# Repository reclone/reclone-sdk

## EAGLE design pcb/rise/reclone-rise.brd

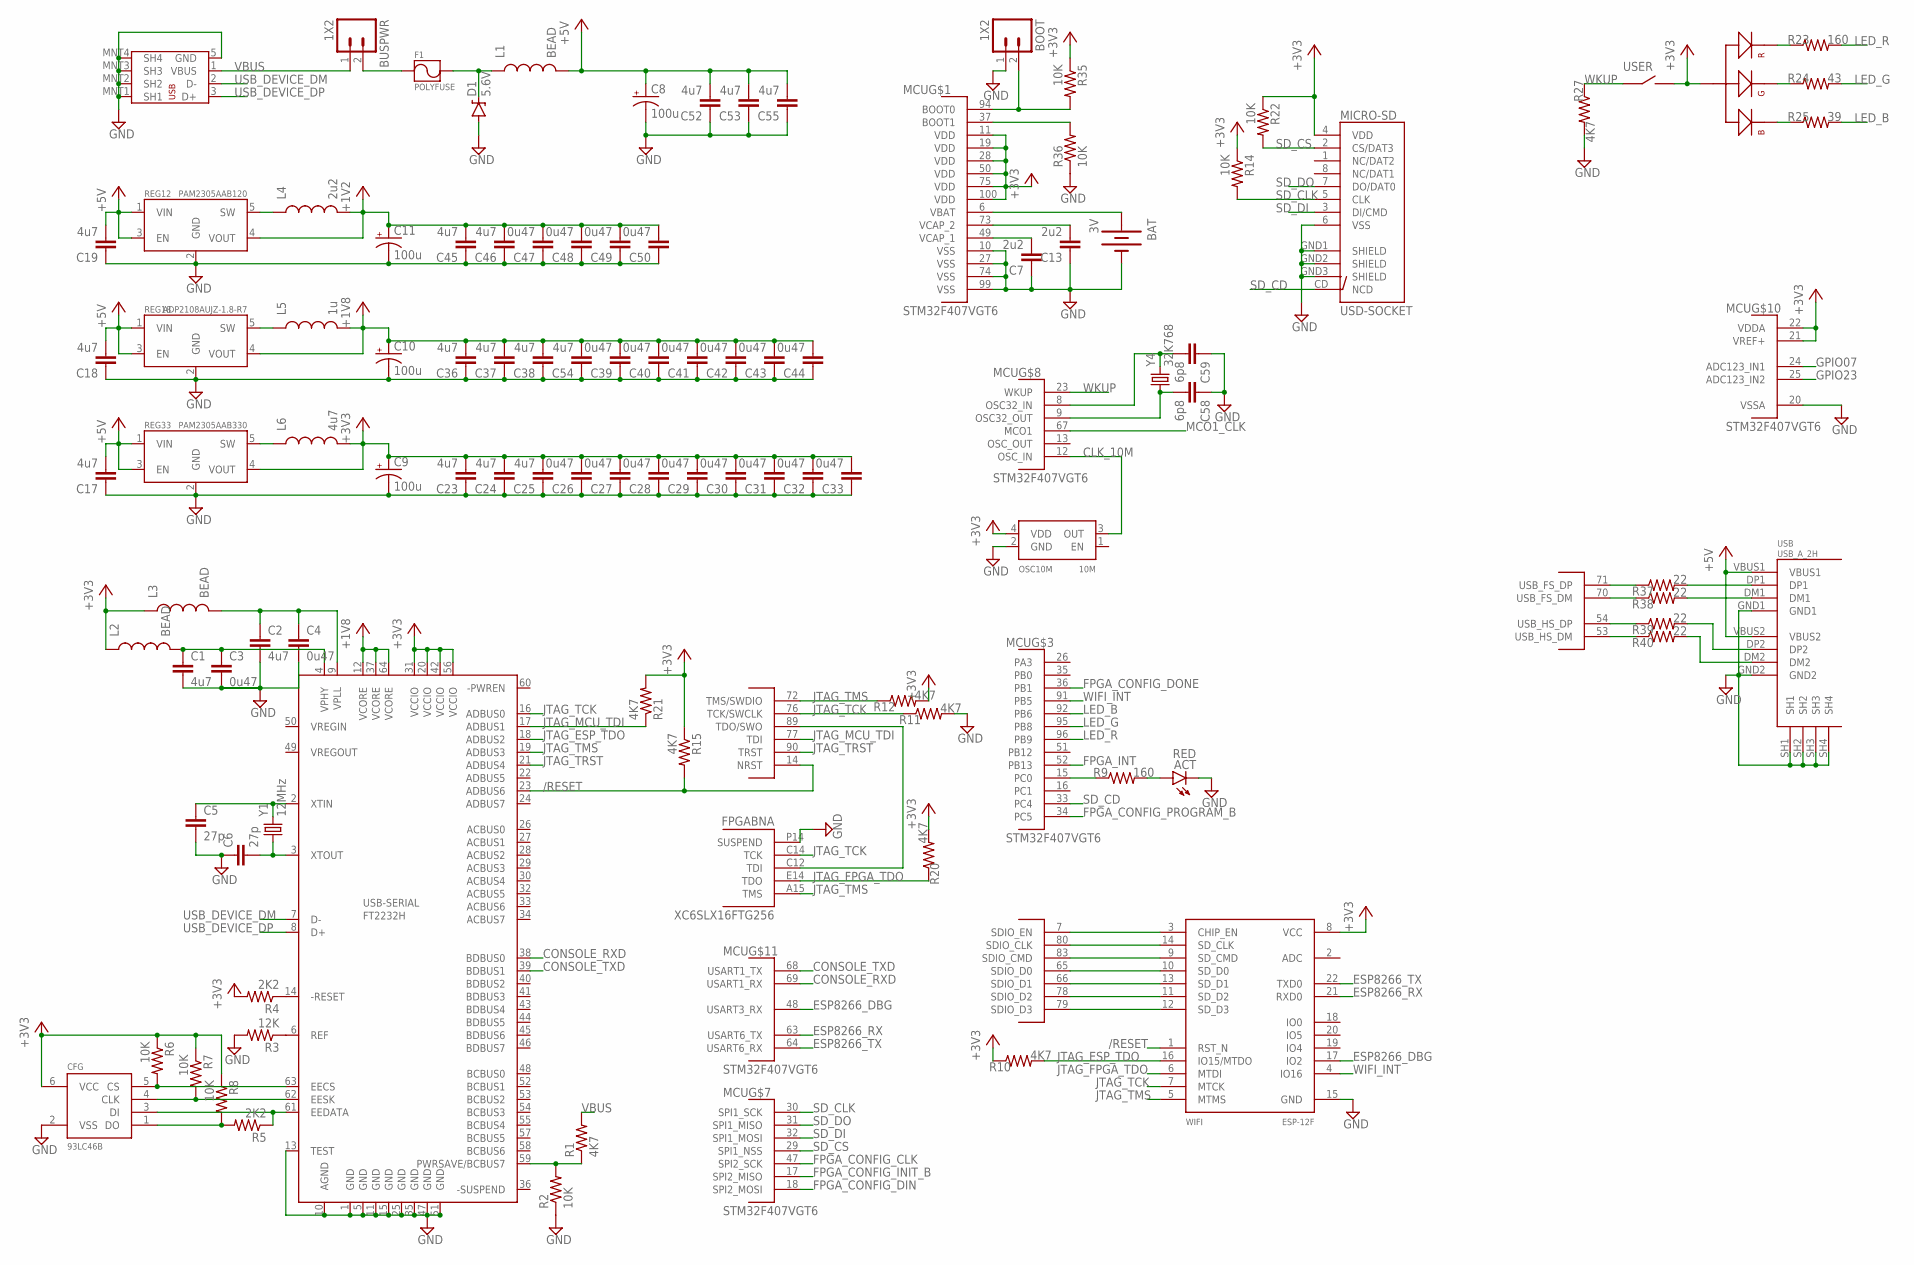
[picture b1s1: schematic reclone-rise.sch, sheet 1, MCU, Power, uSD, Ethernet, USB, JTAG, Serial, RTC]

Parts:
ACT: RED; LED-0603
BAT: 3V; BATTCON_12MM; DIGIKEY# BK-885-ND
BOOT: 1X2; 1X02; DIGIKEY# 952-1770-ND
BUSPWR: 1X2; 1X02; DIGIKEY# 952-1770-ND
C1, C2, C17, C18, C19, C23, C24, C25, C36, C37, C38, C45, C46, C52, C53, C54, C55: 4u7; 0603-CAP
C3, C4, C26, C27, C28, C29, C30, C31, C32, C33, C39, C40, C41, C42, C43, C44, C47, C48, C49, C50: 0u47; 0603-CAP
C5, C6: 27p; 0603-CAP
C7, C13: 2u2; 0603-CAP
C8, C9, C10, C11: 100u; EIA3216
C58, C59: 6p8; 0603-CAP
CFG: 93LC46B; SOT-23-6; DIGIKEY# 93LC46BT-I/OTCT-ND
D1: 5.6V; SOD-323
DEBUG: USB-MICRO-B-SMD; DIGIKEY# 609-4618-1-ND
F1: POLYFUSE; 1206L; DIGIKEY# MF-NSMF150-2CT-ND
FPGA: XC6SLX16FTG256; FT256; DIGIKEY# 122-1672-ND
L1, L2, L3: BEAD; 0603
L4: 2u2; 0603
L5: 1u; 0603
L6: 4u7; 0603
MCU: STM32F407VGT6; LQFP-100
MICRO-SD: USD-SOCKET; MICRO-SD-SOCKET-PP; DIGIKEY# 101-00660-68-6-1-ND
OSC10M: 10M; OSC-5X3.2; DIGIKEY# 631-1436-1-ND
R1, R10, R11, R12, R15, R20, R21, R27: 4K7; 0603-RES
R2, R6, R7, R8, R14, R22, R35, R36: 10K; 0603-RES
R3: 12K; 0603-RES
R4, R5: 2K2; 0603-RES
R9, R23: 160; 0603-RES
R24: 43; 0603-RES
R25: 39; 0603-RES
R37, R38, R39, R40: 22; 0603-RES
REG12: PAM2305AAB120; SOT-23-5; DIGIKEY# PAM2305AAB120DICT-ND
REG18: ADP2108AUJZ-1.8-R7; SOT-23-5; DIGIKEY# ADP2108AUJZ-1.8-R7CT-ND
REG33: PAM2305AAB330; SOT-23-5; DIGIKEY# PAM2305AAB330DICT-ND
RGB: OVSRRGBCC3; RGB_LED_1204_RTANG; DIGIKEY# 365-1410-1-ND
USB: USB_A_2H; USB-A-2H
USB-SERIAL: FT2232H; TQFP64-12X12; DIGIKEY# 768-1024-1-ND
USER: TL1105SF250Q; PB_TACT_RTANG; DIGIKEY# EG1840-ND
WIFI: ESP-12F
Y1: 12MHz; CRYSTAL-SMD-5X3
Y4: 32K768; CRYSTAL-32KHZ-SMD_EPSON_MC146

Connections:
+1V2: C11.A (+), C45.2, C46.2, C47.2, C48.2, C49.2, C50.2, L4.2, REG12.4 (VOUT); also elsewhere on the board
+1V8: C10.A (+), C36.2, C37.2, C38.2, C39.2, C40.2, C41.2, C42.2, C43.2, C44.2, C54.2, L5.2, REG18.4 (VOUT), USB-SERIAL.12 (VCORE), USB-SERIAL.37 (VCORE), USB-SERIAL.64 (VCORE); also elsewhere on the board
+3V3: C9.A (+), C23.2, C24.2, C25.2, C26.2, C27.2, C28.2, C29.2, C30.2, C31.2, C32.2, C33.2, CFG.6 (VCC), L2.1, L3.1, L6.2, MCU.11 (VDD), MCU.19 (VDD), MCU.21 (VREF+), MCU.22 (VDDA), MCU.28 (VDD), MCU.50 (VDD), MCU.75 (VDD), MCU.100 (VDD), MICRO-SD.4 (VDD), OSC10M.4 (VDD), R4.2, R6.1, R7.1, R8.1, R10.1, R12.2, R14.1, R15.1, R20.2, R21.2, R22.1, R35.1, REG33.4 (VOUT), RGB.4 (ANODE), USB-SERIAL.20 (VCCIO), USB-SERIAL.31 (VCCIO), USB-SERIAL.42 (VCCIO), USB-SERIAL.56 (VCCIO), USER.SW_B (B), WIFI.8 (VCC); also elsewhere on the board
+5V: C8.A (+), C17.2, C18.2, C19.2, C52.2, C53.2, C55.2, L1.2, REG12.1 (VIN), REG12.3 (EN), REG18.1 (VIN), REG18.3 (EN), REG33.1 (VIN), REG33.3 (EN), USB.VBUS1, USB.VBUS2; also elsewhere on the board
/RESET: MCU.14 (NRST), R15.2, USB-SERIAL.23 (ADBUS6), WIFI.1 (RST_N)
BOOT0: BOOT.2, MCU.94 (BOOT0), R35.2
BOOT1: MCU.37 (BOOT1), R36.2
CLK_10M: MCU.12 (OSC_IN), OSC10M.3 (OUT); also elsewhere on the board
CONSOLE_RXD: MCU.69 (USART1_RX), USB-SERIAL.38 (BDBUS0)
CONSOLE_TXD: MCU.68 (USART1_TX), USB-SERIAL.39 (BDBUS1)
ESP8266_DBG: MCU.48 (USART3_RX), WIFI.17 (IO2)
ESP8266_RX: MCU.63 (USART6_TX), WIFI.21 (RXD0)
ESP8266_TX: MCU.64 (USART6_RX), WIFI.22 (TXD0)
ESP_CH_EN: MCU.7 (SDIO_EN), WIFI.3 (CHIP_EN)
FPGA_CONFIG_CLK: MCU.47 (SPI2_SCK); also elsewhere on the board
FPGA_CONFIG_DIN: MCU.18 (SPI2_MOSI); also elsewhere on the board
FPGA_CONFIG_DONE: MCU.36 (PB1); also elsewhere on the board
FPGA_CONFIG_INIT_B: MCU.17 (SPI2_MISO); also elsewhere on the board
FPGA_CONFIG_PROGRAM_B: MCU.34 (PC5); also elsewhere on the board
FPGA_INT: MCU.52 (PB13); also elsewhere on the board
GND: ACT.C, BAT.GND (-), BOOT.1, C1.2, C2.2, C3.2, C4.2, C5.2, C6.1, C7.1, C8.C (-), C9.C (-), C10.C (-), C11.C (-), C13.1, C17.1, C18.1, C19.1, C23.1, C24.1, C25.1, C26.1, C27.1, C28.1, C29.1, C30.1, C31.1, C32.1, C33.1, C36.1, C37.1, C38.1, C39.1, C40.1, C41.1, C42.1, C43.1, C44.1, C45.1, C46.1, C47.1, C48.1, C49.1, C50.1, C52.1, C53.1, C54.1, C55.1, C58.1, C59.1, CFG.2 (VSS), D1.A, DEBUG.5 (GND), DEBUG.MNT1 (SH1), DEBUG.MNT2 (SH2), DEBUG.MNT3 (SH3), DEBUG.MNT4 (SH4), FPGA.P14 (SUSPEND), MCU.10 (VSS), MCU.20 (VSSA), MCU.27 (VSS), MCU.74 (VSS), MCU.99 (VSS), MICRO-SD.6 (VSS), MICRO-SD.GND1 (SHIELD), MICRO-SD.GND2 (SHIELD), MICRO-SD.GND3 (SHIELD), OSC10M.2 (GND), R2.1, R3.2, R11.2, R27.2, R36.1, REG12.2 (GND), REG18.2 (GND), REG33.2 (GND), USB.GND1, USB.GND2, USB.SH1, USB.SH2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; also elsewhere on the board
GPIO07: MCU.24 (ADC123_IN1); also elsewhere on the board
GPIO23: MCU.25 (ADC123_IN2); also elsewhere on the board
JTAG_ESP_TDO: R10.2, USB-SERIAL.18 (ADBUS2), WIFI.16 (IO15/MTDO)
JTAG_FPGA_TDO: FPGA.E14 (TDO), R20.1, WIFI.6 (MTDI)
JTAG_MCU_TDI: MCU.77 (TDI), R21.1, USB-SERIAL.17 (ADBUS1)
JTAG_MCU_TDO: FPGA.C12 (TDI), MCU.89 (TDO/SWO)
JTAG_TCK: FPGA.C14 (TCK), MCU.76 (TCK/SWCLK), R11.1, USB-SERIAL.16 (ADBUS0), WIFI.7 (MTCK)
JTAG_TMS: FPGA.A15 (TMS), MCU.72 (TMS/SWDIO), R12.1, USB-SERIAL.19 (ADBUS3), WIFI.5 (MTMS)
JTAG_TRST: MCU.90 (TRST), USB-SERIAL.21 (ADBUS4)
LED_ACT: MCU.15 (PC0), R9.1
LED_B: MCU.92 (PB6), R25.2
LED_G: MCU.95 (PB8), R24.2
LED_R: MCU.96 (PB9), R23.2
MCO1_CLK: MCU.67 (MCO1); also elsewhere on the board
unnamed: MCU.71 (USB_FS_DP), R37.1
unnamed: MCU.70 (USB_FS_DM), R38.1
unnamed: MCU.54 (USB_HS_DP), R39.1
unnamed: MCU.53 (USB_HS_DM), R40.1
unnamed: R40.2, USB.DM2
unnamed: R39.2, USB.DP2
unnamed: R1.1, R2.2, USB-SERIAL.59 (PWRSAVE/BCBUS7)
unnamed: R3.1, USB-SERIAL.6 (REF)
unnamed: R4.1, USB-SERIAL.14 (-RESET)
unnamed: CFG.1 (DO), R5.2, R8.2
unnamed: CFG.3 (DI), R5.1, USB-SERIAL.61 (EEDATA)
unnamed: CFG.4 (CLK), R7.2, USB-SERIAL.62 (EESK)
unnamed: CFG.5 (CS), R6.2, USB-SERIAL.63 (EECS)
unnamed: C2.1, C4.1, L3.2, USB-SERIAL.9 (VPLL)
unnamed: C1.1, C3.1, L2.2, USB-SERIAL.4 (VPHY)
unnamed: C6.2, USB-SERIAL.3 (XTOUT), Y1.1
unnamed: C5.1, USB-SERIAL.2 (XTIN), Y1.3 (2)
unnamed: R23.1, RGB.1 (R)
unnamed: R24.1, RGB.2 (G)
unnamed: R25.1, RGB.3 (B)
unnamed: C58.2, MCU.9 (OSC32_OUT), Y4.P$2 (1)
unnamed: C59.2, MCU.8 (OSC32_IN), Y4.P$1 (2)
unnamed: R37.2, USB.DP1
unnamed: BUSPWR.2, F1.1
unnamed: ACT.A, R9.2
unnamed: R38.2, USB.DM1
unnamed: D1.C, F1.2, L1.1
unnamed: L4.1, REG12.5 (SW)
unnamed: L5.1, REG18.5 (SW)
unnamed: L6.1, REG33.5 (SW)
SDIO_CLK: MCU.80 (SDIO_CLK), WIFI.14 (SD_CLK)
SDIO_CMD: MCU.83 (SDIO_CMD), WIFI.9 (SD_CMD)
SDIO_D0: MCU.65 (SDIO_D0), WIFI.10 (SD_D0)
SDIO_D1: MCU.66 (SDIO_D1), WIFI.13 (SD_D1)
SDIO_D2: MCU.78 (SDIO_D2), WIFI.11 (SD_D2)
SDIO_D3: MCU.79 (SDIO_D3), WIFI.12 (SD_D3)
SD_CD: MCU.33 (PC4), MICRO-SD.CD (NCD)
SD_CLK: MCU.30 (SPI1_SCK), MICRO-SD.5 (CLK), R14.2
SD_CS: MCU.29 (SPI1_NSS), MICRO-SD.2 (CS/DAT3), R22.2
SD_DI: MCU.32 (SPI1_MOSI), MICRO-SD.3 (DI/CMD)
SD_DO: MCU.31 (SPI1_MISO), MICRO-SD.7 (DO/DAT0)
USB_DEVICE_DM: DEBUG.2 (D-), USB-SERIAL.7 (D-)
USB_DEVICE_DP: DEBUG.3 (D+), USB-SERIAL.8 (D+)
VBAT: BAT.PWR@1 (+), MCU.6 (VBAT)
VBUS: BUSPWR.1, DEBUG.1 (VBUS), R1.2
VCAP_1: C7.2, MCU.49 (VCAP_1)
VCAP_2: C13.2, MCU.73 (VCAP_2)
WIFI_INT: MCU.91 (PB5), WIFI.4 (IO16)
WKUP: MCU.23 (WKUP), R27.1, USER.SW_A (A)

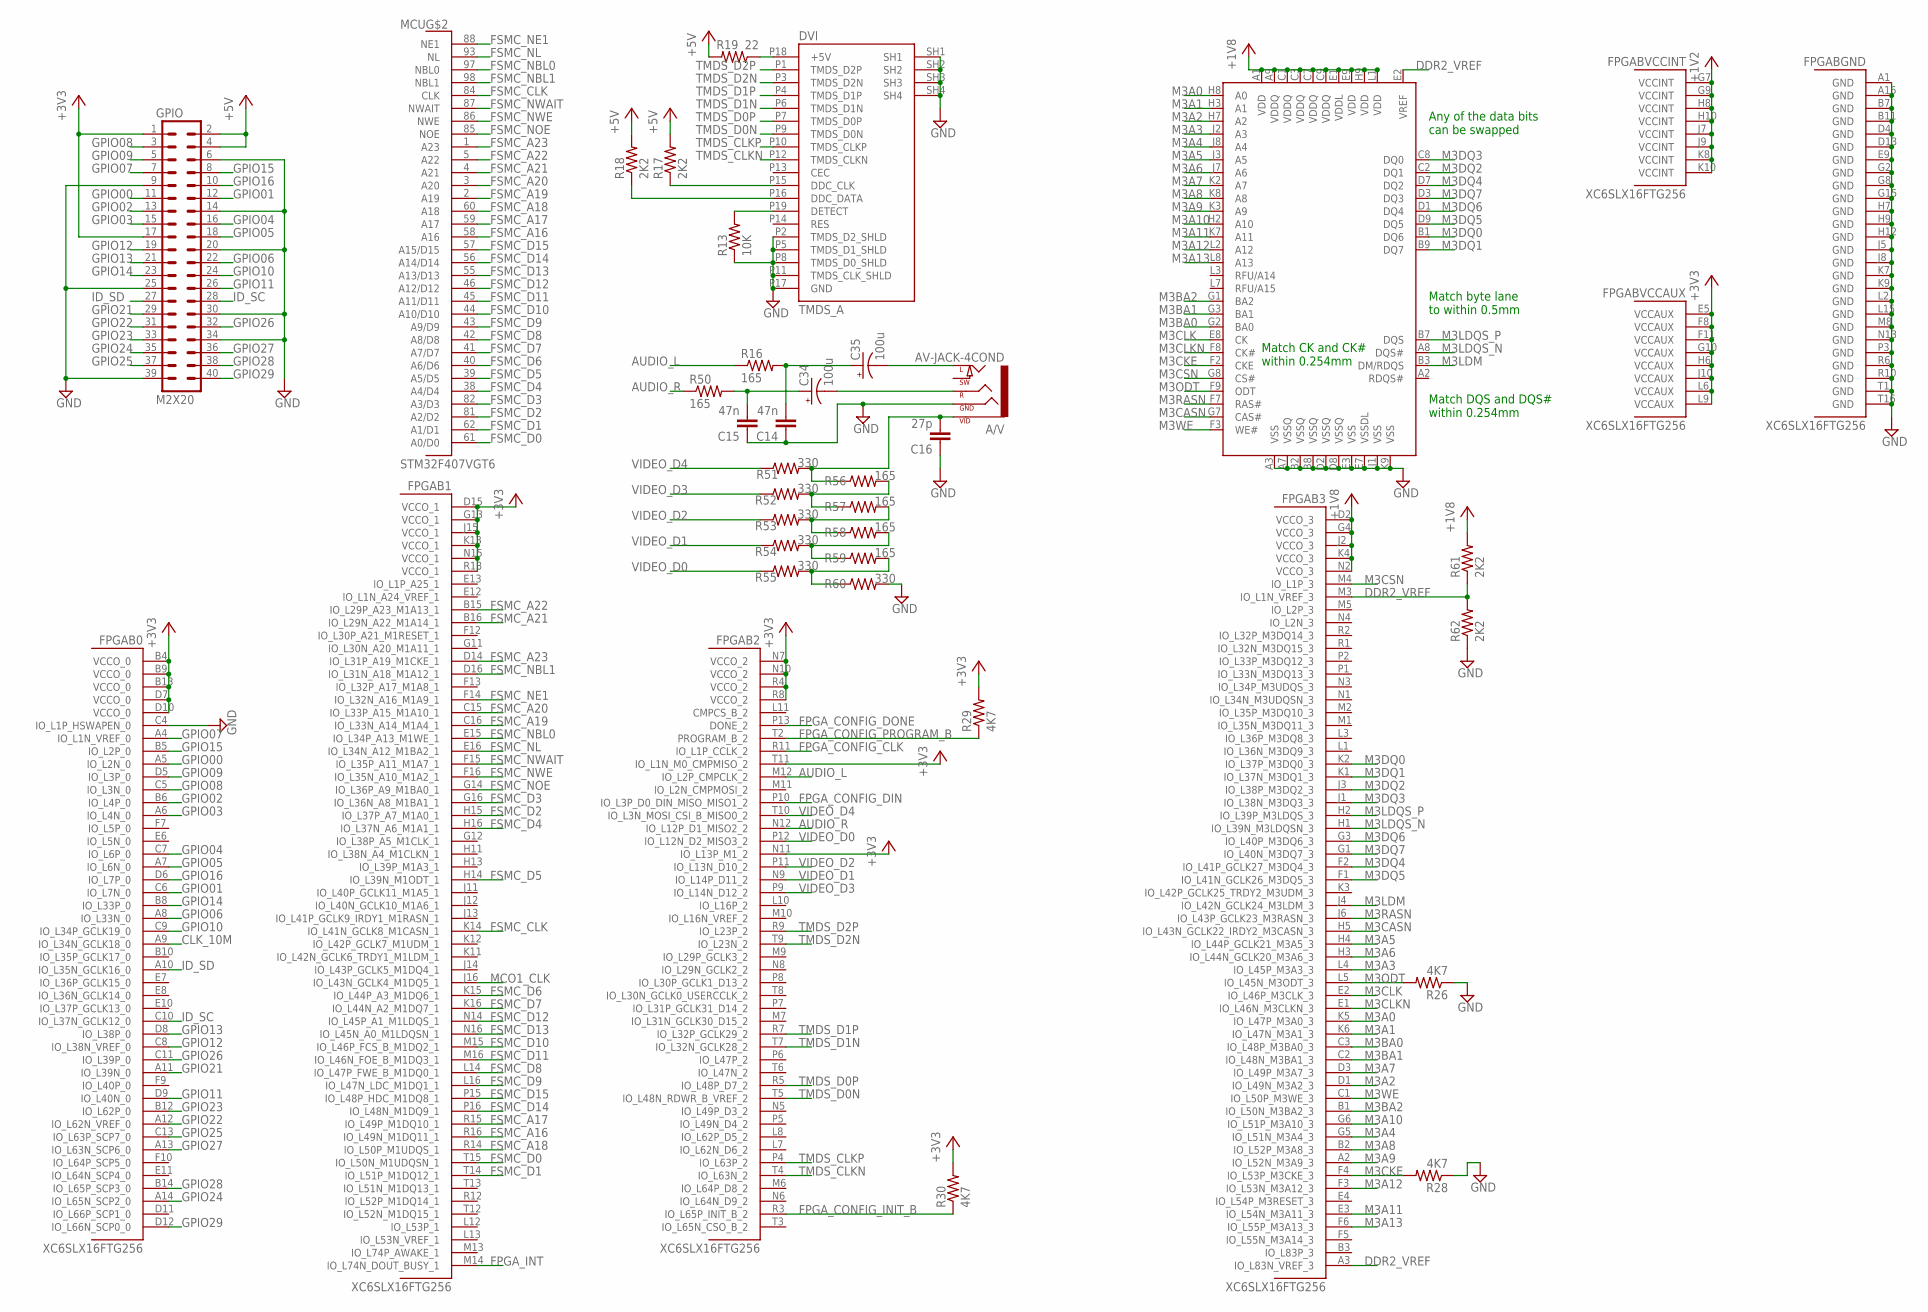
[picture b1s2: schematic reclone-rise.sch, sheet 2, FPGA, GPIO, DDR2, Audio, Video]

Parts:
A/V: AV-JACK-4COND; AV-JACK-3.5MM-4COND-SMD; DIGIKEY# CP-43514SJCT-ND
C14, C15: 47n; 0603-CAP
C16: 27p; 0603-CAP
C34, C35: 100u; EIA3216
DVI: TMDS_A; TMDS_A_SMT; DIGIKEY# 609-4614-1-ND
FPGA: XC6SLX16FTG256; FT256; DIGIKEY# 122-1672-ND
GPIO: M2X20; 2X20; DIGIKEY# S2012EC-20-ND
MCU: STM32F407VGT6; LQFP-100
R13: 10K; 0603-RES
R16, R50, R56, R57, R58, R59: 165; 0603-RES
R17, R18, R61, R62: 2K2; 0603-RES
R19: 22; 0603-RES
R26, R28, R29, R30: 4K7; 0603-RES
R51, R52, R53, R54, R55, R60: 330; 0603-RES
RAM: AS4C128M8D2; 60-FBGA-8X10; DIGIKEY# 1450-1141-ND

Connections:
+1V2: FPGA.G7 (VCCINT), FPGA.G9 (VCCINT), FPGA.H8 (VCCINT), FPGA.H10 (VCCINT), FPGA.J7 (VCCINT), FPGA.J9 (VCCINT), FPGA.K8 (VCCINT), FPGA.K10 (VCCINT); also elsewhere on the board
+1V8: FPGA.D2 (VCCO_3), FPGA.G4 (VCCO_3), FPGA.J2 (VCCO_3), FPGA.K4 (VCCO_3), FPGA.N2 (VCCO_3), R61.2, RAM.A1 (VDD), RAM.A9 (VDDQ), RAM.C1 (VDDQ), RAM.C3 (VDDQ), RAM.C7 (VDDQ), RAM.C9 (VDDQ), RAM.E1 (VDDL), RAM.E9 (VDD), RAM.H9 (VDD), RAM.L1 (VDD); also elsewhere on the board
+3V3: FPGA.B4 (VCCO_0), FPGA.B9 (VCCO_0), FPGA.B13 (VCCO_0), FPGA.D7 (VCCO_0), FPGA.D10 (VCCO_0), FPGA.D15 (VCCO_1), FPGA.E5 (VCCAUX), FPGA.F8 (VCCAUX), FPGA.F11 (VCCAUX), FPGA.G10 (VCCAUX), FPGA.G13 (VCCO_1), FPGA.H6 (VCCAUX), FPGA.J10 (VCCAUX), FPGA.J15 (VCCO_1), FPGA.K13 (VCCO_1), FPGA.L6 (VCCAUX), FPGA.L9 (VCCAUX), FPGA.N7 (VCCO_2), FPGA.N10 (VCCO_2), FPGA.N11 (IO_L13P_M1_2), FPGA.N15 (VCCO_1), FPGA.R4 (VCCO_2), FPGA.R8 (VCCO_2), FPGA.R13 (VCCO_1), FPGA.T11 (IO_L1N_M0_CMPMISO_2), GPIO.1, GPIO.17, R29.2, R30.2; also elsewhere on the board
+5V: GPIO.2, GPIO.4, R17.2, R18.2, R19.2; also elsewhere on the board
AUDIO_L: FPGA.M12 (IO_L2P_CMPCLK_2), R16.1
AUDIO_R: FPGA.N12 (IO_L12P_D1_MISO2_2), R50.1
CLK_10M: FPGA.A9 (IO_L34N_GCLK18_0); also elsewhere on the board
DDR2_VREF: FPGA.A3 (IO_L83N_VREF_3), FPGA.M3 (IO_L1N_VREF_3), R61.1, R62.2, RAM.E2 (VREF)
FPGA_CONFIG_CLK: FPGA.R11 (IO_L1P_CCLK_2); also elsewhere on the board
FPGA_CONFIG_DIN: FPGA.P10 (IO_L3P_D0_DIN_MISO_MISO1_2); also elsewhere on the board
FPGA_CONFIG_DONE: FPGA.P13 (DONE_2); also elsewhere on the board
FPGA_CONFIG_INIT_B: FPGA.R3 (IO_L65P_INIT_B_2), R30.1; also elsewhere on the board
FPGA_CONFIG_PROGRAM_B: FPGA.T2 (PROGRAM_B_2), R29.1; also elsewhere on the board
FPGA_INT: FPGA.M14 (IO_L74N_DOUT_BUSY_1); also elsewhere on the board
FSMC_A16: FPGA.R16 (IO_L49N_M1DQ11_1), MCU.58 (A16)
FSMC_A17: FPGA.R15 (IO_L49P_M1DQ10_1), MCU.59 (A17)
FSMC_A18: FPGA.R14 (IO_L50P_M1UDQS_1), MCU.60 (A18)
FSMC_A19: FPGA.C16 (IO_L33N_A14_M1A4_1), MCU.2 (A19)
FSMC_A20: FPGA.C15 (IO_L33P_A15_M1A10_1), MCU.3 (A20)
FSMC_A21: FPGA.B16 (IO_L29N_A22_M1A14_1), MCU.4 (A21)
FSMC_A22: FPGA.B15 (IO_L29P_A23_M1A13_1), MCU.5 (A22)
FSMC_A23: FPGA.D14 (IO_L31P_A19_M1CKE_1), MCU.1 (A23)
FSMC_CLK: FPGA.K14 (IO_L41N_GCLK8_M1CASN_1), MCU.84 (CLK)
FSMC_D0: FPGA.T15 (IO_L50N_M1UDQSN_1), MCU.61 (A0/D0)
FSMC_D1: FPGA.T14 (IO_L51P_M1DQ12_1), MCU.62 (A1/D1)
FSMC_D2: FPGA.H15 (IO_L37P_A7_M1A0_1), MCU.81 (A2/D2)
FSMC_D3: FPGA.G16 (IO_L36N_A8_M1BA1_1), MCU.82 (A3/D3)
FSMC_D4: FPGA.H16 (IO_L37N_A6_M1A1_1), MCU.38 (A4/D4)
FSMC_D5: FPGA.H14 (IO_L39N_M1ODT_1), MCU.39 (A5/D5)
FSMC_D6: FPGA.K15 (IO_L44P_A3_M1DQ6_1), MCU.40 (A6/D6)
FSMC_D7: FPGA.K16 (IO_L44N_A2_M1DQ7_1), MCU.41 (A7/D7)
FSMC_D8: FPGA.L14 (IO_L47P_FWE_B_M1DQ0_1), MCU.42 (A8/D8)
FSMC_D9: FPGA.L16 (IO_L47N_LDC_M1DQ1_1), MCU.43 (A9/D9)
FSMC_D10: FPGA.M15 (IO_L46P_FCS_B_M1DQ2_1), MCU.44 (A10/D10)
FSMC_D11: FPGA.M16 (IO_L46N_FOE_B_M1DQ3_1), MCU.45 (A11/D11)
FSMC_D12: FPGA.N14 (IO_L45P_A1_M1LDQS_1), MCU.46 (A12/D12)
FSMC_D13: FPGA.N16 (IO_L45N_A0_M1LDQSN_1), MCU.55 (A13/D13)
FSMC_D14: FPGA.P16 (IO_L48N_M1DQ9_1), MCU.56 (A14/D14)
FSMC_D15: FPGA.P15 (IO_L48P_HDC_M1DQ8_1), MCU.57 (A15/D15)
FSMC_NBL0: FPGA.E15 (IO_L34P_A13_M1WE_1), MCU.97 (NBL0)
FSMC_NBL1: FPGA.D16 (IO_L31N_A18_M1A12_1), MCU.98 (NBL1)
FSMC_NE1: FPGA.F14 (IO_L32N_A16_M1A9_1), MCU.88 (NE1)
FSMC_NL: FPGA.E16 (IO_L34N_A12_M1BA2_1), MCU.93 (NL)
FSMC_NOE: FPGA.G14 (IO_L36P_A9_M1BA0_1), MCU.85 (NOE)
FSMC_NWAIT: FPGA.F15 (IO_L35P_A11_M1A7_1), MCU.87 (NWAIT)
FSMC_NWE: FPGA.F16 (IO_L35N_A10_M1A2_1), MCU.86 (NWE)
GND: A/V.RING2 (GND), C14.1, C15.1, C16.1, DVI.P2 (TMDS_D2_SHLD), DVI.P5 (TMDS_D1_SHLD), DVI.P8 (TMDS_D0_SHLD), DVI.P11 (TMDS_CLK_SHLD), DVI.P17 (GND), DVI.SH1, DVI.SH2, DVI.SH3, DVI.SH4, FPGA.A1 (GND), FPGA.A16 (GND), FPGA.B7 (GND), FPGA.B11 (GND), FPGA.C4 (IO_L1P_HSWAPEN_0), FPGA.D4 (GND), FPGA.D13 (GND), FPGA.E9 (GND), FPGA.G2 (GND), FPGA.G8 (GND), FPGA.G15 (GND), FPGA.H7 (GND), FPGA.H9 (GND), FPGA.H12 (GND), FPGA.J5 (GND), FPGA.J8 (GND), FPGA.K7 (GND), FPGA.K9 (GND), FPGA.L2 (GND), FPGA.L15 (GND), FPGA.M8 (GND), FPGA.N13 (GND), FPGA.P3 (GND), FPGA.R6 (GND), FPGA.R10 (GND), FPGA.T1 (GND), FPGA.T16 (GND), GPIO.6, GPIO.9, GPIO.14, GPIO.20, GPIO.25, GPIO.30, GPIO.34, GPIO.39, R13.1, R26.1, R28.1, R60.2, R62.1, RAM.A3 (VSS), RAM.A7 (VSSQ), RAM.B2 (VSSQ), RAM.B8 (VSSQ), RAM.D2 (VSSQ), RAM.D8 (VSSQ), RAM.E3 (VSS), RAM.E7 (VSSDL), RAM.J1 (VSS), RAM.K9 (VSS); also elsewhere on the board
GPIO00: FPGA.A5 (IO_L2N_0), GPIO.11
GPIO01: FPGA.C6 (IO_L7N_0), GPIO.12
GPIO02: FPGA.B6 (IO_L4P_0), GPIO.13
GPIO03: FPGA.A6 (IO_L4N_0), GPIO.15
GPIO04: FPGA.C7 (IO_L6P_0), GPIO.16
GPIO05: FPGA.A7 (IO_L6N_0), GPIO.18
GPIO06: FPGA.A8 (IO_L33N_0), GPIO.22
GPIO07: FPGA.A4 (IO_L1N_VREF_0), GPIO.7; also elsewhere on the board
GPIO08: FPGA.C5 (IO_L3N_0), GPIO.3
GPIO09: FPGA.D5 (IO_L3P_0), GPIO.5
GPIO10: FPGA.C9 (IO_L34P_GCLK19_0), GPIO.24
GPIO11: FPGA.D9 (IO_L40N_0), GPIO.26
GPIO12: FPGA.C8 (IO_L38N_VREF_0), GPIO.19
GPIO13: FPGA.D8 (IO_L38P_0), GPIO.21
GPIO14: FPGA.B8 (IO_L33P_0), GPIO.23
GPIO15: FPGA.B5 (IO_L2P_0), GPIO.8
GPIO16: FPGA.D6 (IO_L7P_0), GPIO.10
GPIO21: FPGA.A11 (IO_L39N_0), GPIO.29
GPIO22: FPGA.A12 (IO_L62N_VREF_0), GPIO.31
GPIO23: FPGA.B12 (IO_L62P_0), GPIO.33; also elsewhere on the board
GPIO24: FPGA.A14 (IO_L65N_SCP2_0), GPIO.35
GPIO25: FPGA.C13 (IO_L63P_SCP7_0), GPIO.37
GPIO26: FPGA.C11 (IO_L39P_0), GPIO.32
GPIO27: FPGA.A13 (IO_L63N_SCP6_0), GPIO.36
GPIO28: FPGA.B14 (IO_L65P_SCP3_0), GPIO.38
GPIO29: FPGA.D12 (IO_L66N_SCP0_0), GPIO.40
ID_SC: FPGA.C10 (IO_L37N_GCLK12_0), GPIO.28
ID_SD: FPGA.A10 (IO_L35N_GCLK16_0), GPIO.27
M3A0: FPGA.K5 (IO_L47P_M3A0_3), RAM.H8 (A0)
M3A1: FPGA.K6 (IO_L47N_M3A1_3), RAM.H3 (A1)
M3A2: FPGA.D1 (IO_L49N_M3A2_3), RAM.H7 (A2)
M3A3: FPGA.L4 (IO_L45P_M3A3_3), RAM.J2 (A3)
M3A4: FPGA.G5 (IO_L51N_M3A4_3), RAM.J8 (A4)
M3A5: FPGA.H4 (IO_L44P_GCLK21_M3A5_3), RAM.J3 (A5)
M3A6: FPGA.H3 (IO_L44N_GCLK20_M3A6_3), RAM.J7 (A6)
M3A7: FPGA.D3 (IO_L49P_M3A7_3), RAM.K2 (A7)
M3A8: FPGA.B2 (IO_L52P_M3A8_3), RAM.K8 (A8)
M3A9: FPGA.A2 (IO_L52N_M3A9_3), RAM.K3 (A9)
M3A10: FPGA.G6 (IO_L51P_M3A10_3), RAM.H2 (A10)
M3A11: FPGA.E3 (IO_L54N_M3A11_3), RAM.K7 (A11)
M3A12: FPGA.F3 (IO_L53N_M3A12_3), RAM.L2 (A12)
M3A13: FPGA.F6 (IO_L55P_M3A13_3), RAM.L8 (A13)
M3BA0: FPGA.C3 (IO_L48P_M3BA0_3), RAM.G2 (BA0)
M3BA1: FPGA.C2 (IO_L48N_M3BA1_3), RAM.G3 (BA1)
M3BA2: FPGA.B1 (IO_L50N_M3BA2_3), RAM.G1 (BA2)
M3CASN: FPGA.H5 (IO_L43N_GCLK22_IRDY2_M3CASN_3), RAM.G7 (CAS#)
M3CKE: FPGA.F4 (IO_L53P_M3CKE_3), R28.2, RAM.F2 (CKE)
M3CLK: FPGA.E2 (IO_L46P_M3CLK_3), RAM.E8 (CK)
M3CLKN: FPGA.E1 (IO_L46N_M3CLKN_3), RAM.F8 (CK#)
M3CSN: FPGA.M4 (IO_L1P_3), RAM.G8 (CS#)
M3DQ0: FPGA.K2 (IO_L37P_M3DQ0_3), RAM.B1 (DQ6)
M3DQ1: FPGA.K1 (IO_L37N_M3DQ1_3), RAM.B9 (DQ7)
M3DQ2: FPGA.J3 (IO_L38P_M3DQ2_3), RAM.C2 (DQ1)
M3DQ3: FPGA.J1 (IO_L38N_M3DQ3_3), RAM.C8 (DQ0)
M3DQ4: FPGA.F2 (IO_L41P_GCLK27_M3DQ4_3), RAM.D7 (DQ2)
M3DQ5: FPGA.F1 (IO_L41N_GCLK26_M3DQ5_3), RAM.D9 (DQ5)
M3DQ6: FPGA.G3 (IO_L40P_M3DQ6_3), RAM.D1 (DQ4)
M3DQ7: FPGA.G1 (IO_L40N_M3DQ7_3), RAM.D3 (DQ3)
M3LDM: FPGA.J4 (IO_L42N_GCLK24_M3LDM_3), RAM.B3 (DM/RDQS)
M3LDQS_N: FPGA.H1 (IO_L39N_M3LDQSN_3), RAM.A8 (DQS#)
M3LDQS_P: FPGA.H2 (IO_L39P_M3LDQS_3), RAM.B7 (DQS)
M3ODT: FPGA.L5 (IO_L45N_M3ODT_3), R26.2, RAM.F9 (ODT)
M3RASN: FPGA.J6 (IO_L43P_GCLK23_M3RASN_3), RAM.F7 (RAS#)
M3WE: FPGA.C1 (IO_L50P_M3WE_3), RAM.F3 (WE#)
MCO1_CLK: FPGA.J16 (IO_L43N_GCLK4_M1DQ5_1); also elsewhere on the board
unnamed: DVI.P19 (DETECT), R13.2
unnamed: DVI.P15 (DDC_CLK), R17.1
unnamed: DVI.P16 (DDC_DATA), R18.1
unnamed: DVI.P18 (+5V), R19.1
unnamed: A/V.RING1 (R), C34.C (-)
unnamed: A/V.TIP (L), C35.C (-)
unnamed: C14.2, C35.A (+), R16.2
unnamed: C15.2, C34.A (+), R50.2
unnamed: A/V.SLEEVE (VID), C16.2, R51.2, R56.1
unnamed: R52.2, R56.2, R57.1
unnamed: R53.2, R57.2, R58.1
unnamed: R54.2, R58.2, R59.1
unnamed: R55.2, R59.2, R60.1
TMDS_CLKN: DVI.P12 (TMDS_CLKN), FPGA.T4 (IO_L63N_2)
TMDS_CLKP: DVI.P10 (TMDS_CLKP), FPGA.P4 (IO_L63P_2)
TMDS_D0N: DVI.P9 (TMDS_D0N), FPGA.T5 (IO_L48N_RDWR_B_VREF_2)
TMDS_D0P: DVI.P7 (TMDS_D0P), FPGA.R5 (IO_L48P_D7_2)
TMDS_D1N: DVI.P6 (TMDS_D1N), FPGA.T7 (IO_L32N_GCLK28_2)
TMDS_D1P: DVI.P4 (TMDS_D1P), FPGA.R7 (IO_L32P_GCLK29_2)
TMDS_D2N: DVI.P3 (TMDS_D2N), FPGA.T9 (IO_L23N_2)
TMDS_D2P: DVI.P1 (TMDS_D2P), FPGA.R9 (IO_L23P_2)
VIDEO_D0: FPGA.P12 (IO_L12N_D2_MISO3_2), R55.1
VIDEO_D1: FPGA.N9 (IO_L14P_D11_2), R54.1
VIDEO_D2: FPGA.P11 (IO_L13N_D10_2), R53.1
VIDEO_D3: FPGA.P9 (IO_L14N_D12_2), R52.1
VIDEO_D4: FPGA.T10 (IO_L3N_MOSI_CSI_B_MISO0_2), R51.1

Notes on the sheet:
Any of the data bits can be swapped
Match byte lane to within 0.5mm
Match DQS and DQS# within 0.254mm
Match CK and CK# within 0.254mm

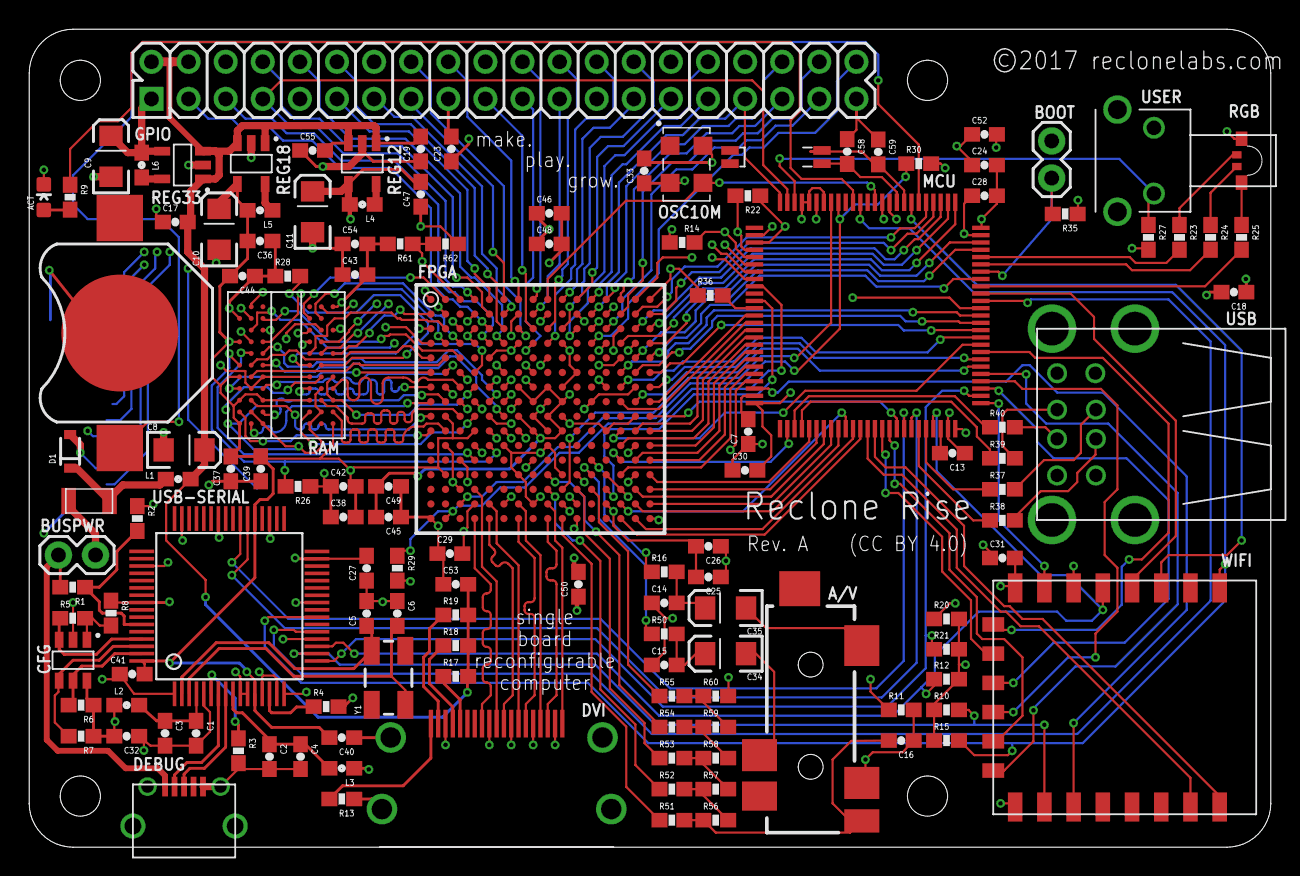
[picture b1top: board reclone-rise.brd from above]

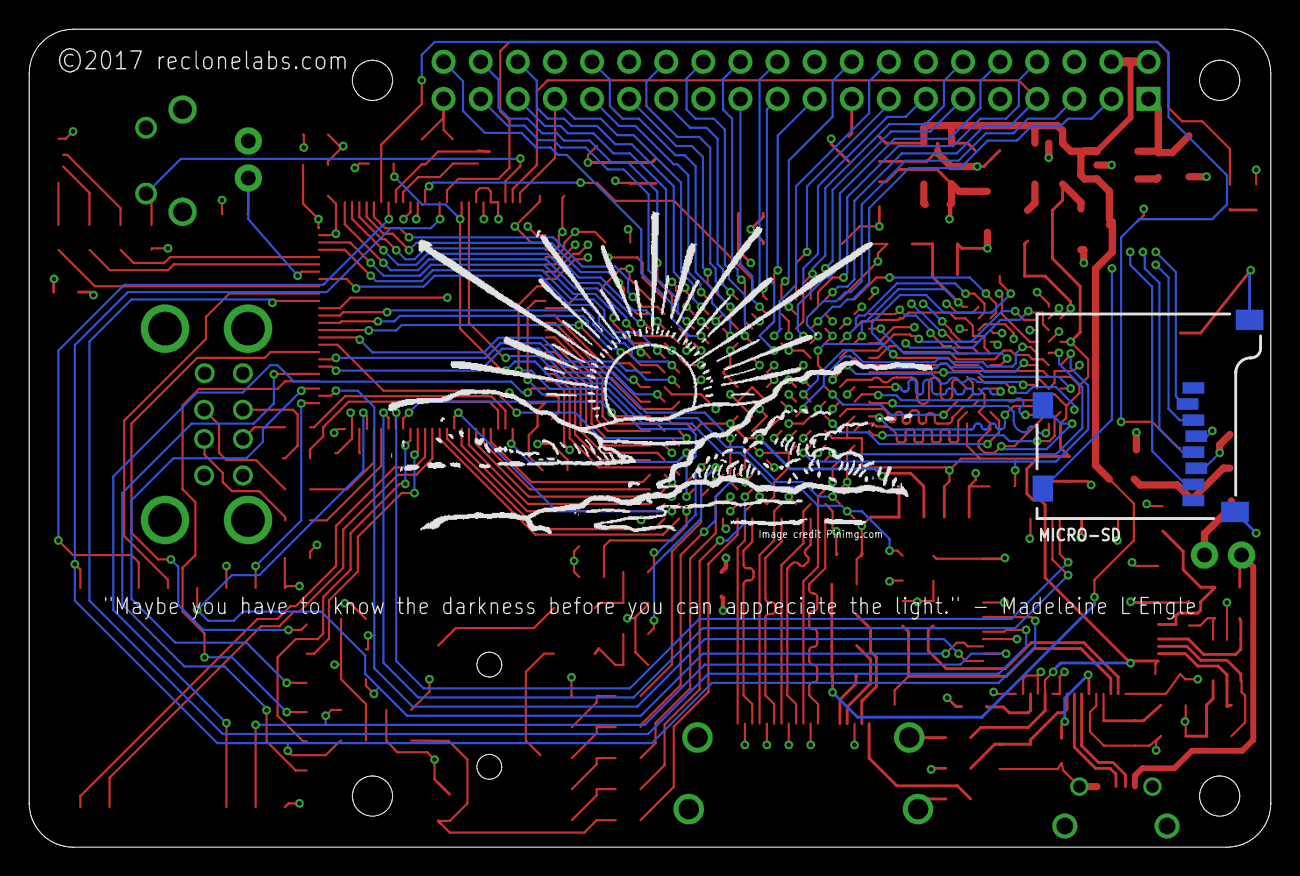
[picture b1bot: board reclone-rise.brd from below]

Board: 4 copper layers, 85.0 x 56.0 mm, 134 parts (2 on the bottom side), 207 nets.

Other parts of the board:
U$8: SUNRISE-GRAPHIC

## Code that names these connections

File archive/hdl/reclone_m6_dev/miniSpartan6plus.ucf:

CONFIG VCCAUX = 3.3;

# Clocks
NET "Clk50" PERIOD = 20 ns | IOSTANDARD=LVCMOS33 | LOC = "K3"; # IO_L42P_GCLK25_TRDY2_M3UDM
NET "Clk32" PERIOD = 31.25 ns | IOSTANDARD=LVCMOS33 | LOC = "J4"; # IO_L42N_GCLK24_M3LDM_3

# LEDs
NET "Leds<0>" LOC="P11" | IOSTANDARD=LVTTL | DRIVE=8 | SLEW=SLOW;
NET "Leds<1>" LOC="N9"  | IOSTANDARD=LVTTL | DRIVE=8 | SLEW=SLOW;
NET "Leds<2>" LOC="M9"  | IOSTANDARD=LVTTL | DRIVE=8 | SLEW=SLOW;
NET "Leds<3>" LOC="P9"  | IOSTANDARD=LVTTL | DRIVE=8 | SLEW=SLOW;
NET "Leds<4>" LOC="T8"  | IOSTANDARD=LVTTL | DRIVE=8 | SLEW=SLOW;
NET "Leds<5>" LOC="N8"  | IOSTANDARD=LVTTL | DRIVE=8 | SLEW=SLOW;
NET "Leds<6>" LOC="P8"  | IOSTANDARD=LVTTL | DRIVE=8 | SLEW=SLOW;
NET "Leds<7>" LOC="P7"  | IOSTANDARD=LVTTL | DRIVE=8 | SLEW=SLOW;

# DVI-D interface
#J3
#NET "TMDS_Out_P(0)"  LOC = "C13" | IOSTANDARD = TMDS_33; # Blue
#NET "TMDS_Out_N(0)"  LOC = "A13" | IOSTANDARD = TMDS_33;
#NET "TMDS_Out_P(1)"  LOC = "B12" | IOSTANDARD = TMDS_33; # Red
#NET "TMDS_Out_N(1)"  LOC = "A12" | IOSTANDARD = TMDS_33;
#NET "TMDS_Out_P(2)"  LOC = "C11" | IOSTANDARD = TMDS_33; # Green
#NET "TMDS_Out_N(2)"  LOC = "A11" | IOSTANDARD = TMDS_33;
#NET "TMDS_Out_P(3)"  LOC = "B14" | IOSTANDARD = TMDS_33; # Clock
#NET "TMDS_Out_N(3)"  LOC = "A14" | IOSTANDARD = TMDS_33;

#J2
NET "TMDS_Out_P(0)"  LOC = "C7" | IOSTANDARD = TMDS_33 | DRIVE=24 | SLEW=FAST; # Blue
NET "TMDS_Out_N(0)"  LOC = "A7" | IOSTANDARD = TMDS_33 | DRIVE=24 | SLEW=FAST;
NET "TMDS_Out_P(1)"  LOC = "B6" | IOSTANDARD = TMDS_33 | DRIVE=24 | SLEW=FAST; # Red
NET "TMDS_Out_N(1)"  LOC = "A6" | IOSTANDARD = TMDS_33 | DRIVE=24 | SLEW=FAST;
NET "TMDS_Out_P(2)"  LOC = "B5" | IOSTANDARD = TMDS_33 | DRIVE=24 | SLEW=FAST; # Green
NET "TMDS_Out_N(2)"  LOC = "A5" | IOSTANDARD = TMDS_33 | DRIVE=24 | SLEW=FAST;
NET "TMDS_Out_P(3)"  LOC = "C9" | IOSTANDARD = TMDS_33 | DRIVE=24 | SLEW=FAST; # Clock
NET "TMDS_Out_N(3)"  LOC = "A9" | IOSTANDARD = TMDS_33 | DRIVE=24 | SLEW=FAST;

# DIP Switches
NET "Switches(0)"    LOC="L1" | IOSTANDARD=LVTTL | PULLUP;
NET "Switches(1)"    LOC="L3" | IOSTANDARD=LVTTL | PULLUP;
NET "Switches(2)"    LOC="L4" | IOSTANDARD=LVTTL | PULLUP;
NET "Switches(3)"    LOC="L5" | IOSTANDARD=LVTTL | PULLUP;

# PSRAM Interface
#                                                  STM32F4 - m6 - Spartan6
NET "FSMC_D(0)"      LOC="D8" | IOSTANDARD=LVCMOS33 | SLEW = FAST; #PD14 - A2 - D8
NET "FSMC_D(1)"      LOC="C8" | IOSTANDARD=LVCMOS33 | SLEW = FAST; #PD15 - A1 - C8
NET "FSMC_D(2)"      LOC="C6" | IOSTANDARD=LVCMOS33 | SLEW = FAST; #PD0  - D1 - C6
NET "FSMC_D(3)"      LOC="C5" | IOSTANDARD=LVCMOS33 | SLEW = FAST; #PD1  - D3 - C5
NET "FSMC_D(4)"      LOC="G14"| IOSTANDARD=LVCMOS33 | SLEW = FAST; #PE7  - B9 - G14
NET "FSMC_D(5)"      LOC="G12"| IOSTANDARD=LVCMOS33 | SLEW = FAST; #PE8  - B8 - G12
NET "FSMC_D(6)"      LOC="F14"| IOSTANDARD=LVCMOS33 | SLEW = FAST; #PE9  - B7 - F14
NET "FSMC_D(7)"      LOC="F12"| IOSTANDARD=LVCMOS33 | SLEW = FAST; #PE10 - B6 - F12
NET "FSMC_D(8)"      LOC="F13"| IOSTANDARD=LVCMOS33 | SLEW = FAST; #PE11 - B5 - F13
NET "FSMC_D(9)"      LOC="E13"| IOSTANDARD=LVCMOS33 | SLEW = FAST; #PE12 - B4 - E13
NET "FSMC_D(10)"     LOC="E12"| IOSTANDARD=LVCMOS33 | SLEW = FAST; #PE13 - B3 - E12
NET "FSMC_D(11)"     LOC="D12"| IOSTANDARD=LVCMOS33 | SLEW = FAST; #PE14 - B2 - D12
NET "FSMC_D(12)"     LOC="D14"| IOSTANDARD=LVCMOS33 | SLEW = FAST; #PE15 - B1 - D14
NET "FSMC_D(13)"     LOC="E10"| IOSTANDARD=LVCMOS33 | SLEW = FAST; #PD10 - A8 - E10
NET "FSMC_D(14)"     LOC="C10"| IOSTANDARD=LVCMOS33 | SLEW = FAST; #PD10 - A7 - C10
NET "FSMC_D(15)"     LOC="B10"| IOSTANDARD=LVCMOS33 | SLEW = FAST; #PD10 - A6 - B10
NET "FSMC_A(16)"     LOC="A10"| IOSTANDARD=LVCMOS33; #PD11 - A5 - A10
NET "FSMC_A(17)"     LOC="D9" | IOSTANDARD=LVCMOS33; #PD12 - A4 - D9
NET "FSMC_A(18)"     LOC="E8" | IOSTANDARD=LVCMOS33; #PD13 - A3 - E8
NET "FSMC_A(19)"     LOC="B2" | IOSTANDARD=LVCMOS33; #PE3  - E6 - B2
NET "FSMC_A(20)"     LOC="D3" | IOSTANDARD=LVCMOS33; #PE4  - E9 - D3
NET "FSMC_A(21)"     LOC="C2" | IOSTANDARD=LVCMOS33; #PE5  - E8 - C2
NET "FSMC_A(22)"     LOC="E3" | IOSTANDARD=LVCMOS33; #PE6  - E11- E3

NET "FSMC_NOE"       LOC="E6" | IOSTANDARD=LVCMOS33 | PULLUP; #PD4  - D2 - E6
NET "FSMC_NWE"       LOC="A3" | IOSTANDARD=LVCMOS33 | PULLUP; #PD5  - E3 - A3
NET "FSMC_NWAIT"     LOC="G5" | IOSTANDARD=LVCMOS33 | SLEW = FAST; #PD6  - E2 - G5
NET "FSMC_NE1_NCE2"  LOC="A2" | IOSTANDARD=LVCMOS33 | PULLUP; #PD7  - E5 - A2
NET "FSMC_NL"        LOC="B3" | IOSTANDARD=LVCMOS33 | PULLUP; #PB7  - E4 - B3
NET "FSMC_NBL(0)"    LOC="G3" | IOSTANDARD=LVCMOS33 | PULLUP; #PE0  - F5 - G3
NET "FSMC_NBL(1)"    LOC="F5" | IOSTANDARD=LVCMOS33 | PULLUP; #PE1  - F4 - F5
NET "FSMC_CLK"       LOC="H3" | IOSTANDARD=LVCMOS33; #PD3  - F8 - H3

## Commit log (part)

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2018-02-25 Finished draft of RegisterFile2Read1Write
2018-03-03 Starting to elaborate the opcode decoding logic and ROM contents
2018-03-11 Adding Verilog files to CMake static library so that they show up in IDE
2018-04-23 Moved some constants to separate headers, and started to elaborate the ALU's adder logic
2018-10-15 Fixed bottom keepout around mounting holes to match top keepout; increased pad length for microsd connector for easier hand soldering and inspection; added 8x10.5 package for DDR2
2018-10-25 Reclone Rise Rev C with updated footprints, better placement of names in silkscreen, and gerbers
2018-10-27 Updated Reclone Rise Rev C gerbers with the new artwork
2019-10-26 Working Blinky SoC example. Completed NGDBUILD_OPTS, MAP_OPTS, PAR_OPTS to match example ISE project; leaving output from ISE tools in cmake output; LVTTL standard on GPIO pins.
2019-11-17 Instantiated a DCM that outputs 90 MHz
2019-11-20 Rough draft of complete ClockGen.v; added "`default_nettype none" to a few files for stricter Verilog
2019-11-21 Change speed grade to -2
2019-12-29 EOF newline
2019-12-31 Added verilator config for CtlEncoder2to10
2019-12-31 Added verilator config for RgbEncoder8to10
2019-12-31 Rename .cc to .cpp for personal preference
2020-01-02 Add missing CMakeLists.txt for CtlEncoder2to10 unit test
2020-01-02 Seed random number generator
2020-01-02 Added first draft of VideoFormatTiming.v
2020-01-02 Video timing unit tests for select vga, svga, and xga timing modes
2020-01-02 Clean up formatting of the vsync expression
2020-01-03 Started DviEncoder.v
2020-01-05 Added Gray counter module and its unit tests
2020-01-07 Making reads from mem a cycle faster to match typical use cases
2020-01-08 Initial unit test for AsyncFifo
2020-01-09 Finished OneWriteOneRead test; changed AsyncFifo back to having a registered ReadData output
2020-01-11 Working DVI output at 720p (green screen)
2020-01-15 First draft of BCH ECC encoders
2020-01-16 Rough draft of NullDataIslandPacket.v and AudioClockRegenPacket.v
2020-01-17 Capitalize Infoframe as InfoFrame for consistency
2020-01-17 CMake configuration for VNullDataIslandPacket
2020-01-18 First draft of DataIslandPacketSerializer.v
2020-01-19 Speed up VideoFormatTimingTests by flushing trace output every frame instead of every line
2020-01-25 Finished RgbToYiq and unit tests
2020-01-30 Incomplete draft of NtscTiming
2020-02-03 Partway through unit test for NTSC interlaced timing
2020-02-06 Fixed vPos calculation for interlace, and added trace logging
2020-02-10 Unit test for color burst waveform based on C++-computed cosine values
2020-02-15 Basic composite video working, but with wrong colors. Green looks orangeish.
2020-02-17 Implemented SMPTE color bars test pattern for NTSC; made NTSC generator treat Y as signed so that the test pattern can generate "blacker than black"
2020-02-18 AvTestPatterns core with NTSC composite video output and SMPTE color bars
2020-02-19 Complete rough draft of PalTiming
2020-02-20 Fixed PalTiming with believed-working timing outputs
2020-02-20 Fixed comments to reflect that it is now the tenth line that gets shortened to do the phase alternation
2020-02-21 Barely working PAL color bars with wrong colors and flickery crap
2020-03-28 Fixed up NtscGeneratorTests after adding pipelining and proper color burst phase
2020-05-09 Fixed up comments for PalGenerator using the comments from NtscGenerator as a template
2020-05-17 Finished fixed-value and random tests in DataIslandPacketSerializerTests, and fixed some bugs in the BCH calculation
2020-05-19 Finished VBlankDataIslandTests
2020-05-19 Implemented missing preamble for VBlankDataIsland
2020-05-19 Refactor VBlankDataIsland to keep track by itself which packet it needs to transmit next
2020-05-25 Setting color encoding back to RGB
2020-05-30 Add AudioDeltaSigmaDacTests
2020-05-30 Add ClockEnableDividerTests
2020-05-30 Set default composite video test pattern back to NTSC
2020-05-31 Use CMake to copy sine1khz.mem to the same binary directory as testSine1kHzTone
2020-06-06 Added SpdInfoFramePacketTests
2020-06-09 Added SpdifChannelStatusTests
2020-06-13 First draft implementation of HBlankDataIsland
2020-06-14 First draft integration of HDMI audio into AvTestPatterns; audio is NOT working yet.
2020-06-16 Moving the HBlankDataIsland till after the HSync region, for nicer looking traces. Audio is working on a monitor but seems muted on the cheap TV.
2020-06-28 Working HDMI audio after fixing BCH ECC calculation in DataIslandPacketSerializer; everything needs a lot of cleanup now because there was a lot of hack and slash to get here
2020-06-28 Update comments in HBlankDataIsland, DataIslandPacketSerializer, and VBlankDataIsland; refactor VBlankDataIsland to react to the active edge of HSync and guarantee its keep-away from HBlankDataIsland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
2020-07-05 Reorganized async-fifo to fifo/async
2020-07-05 Reverted 'c' bit to 1 for 'copyright not asserted'; reverted original sample frequency value to 0 for 'not specified'; fixed SpdifChannelStatusTests
2020-07-05 Fix VBlankDataIslandTests after refactoring VBlankDataIsland to be placed later, accommodating a longer HBlankDataIsland
2020-08-02 Apparently working Hd720p60GreenScreen unit test of VideoTimingSink
2020-08-03 Added proper line padding in bitmap file generator
2020-10-12 Added LoadRedBluePatternTestBitmap
2020-10-13 Completed VideoGeneratorSourceTests.ReplicateBitmap which connects the generator source to the timing sink, and proves that a test bitmap can be passed through relatively unscathed. Added VideoTiming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
2020-12-01 Initial commit of VideoIntegerScaleTests
2020-12-01 Added VideoIntegerScaleTests.OneRequestOneResponse test and fixed a couple design issues and off-by-one errors in VideoIntegerScale
2021-01-31 Implemented BmpPipelineSource and BmpPipelineSink
2021-02-01 Fixed off-by-one issue with BmpPipelineSource; improved test image, but row length still is not correct
2021-02-02 Implemented working vertical scanlines in VideoIntegerScale
2021-02-02 Finished unit tests for VideoCroppingFilter including a better working BmpPipelineSource
2021-02-08 Another partial draft of VideoPaddingFilter.v
2021-02-08 Completed working VideoPaddingFilter with unit tests for padding and trimming
2021-03-06 Finished placing all components in a layout that accommodates both JTAG headers. Some routing remains.
2021-03-12 Cleaned up alignment and routing some more; added DDR2 VRef capacitor; completed BOM attributes with in-stock Digikey parts
2021-04-03 Added verilator target for VideoBinningFilter and corrected syntax error
2021-04-04 Reduced number of cycles in VideoBinningFilterTests from 4000000 to 2500000
2021-04-11 Initial draft of the downstream request portion of VideoNonIntegerScale
2021-05-17 Start defining microcode ROM for 6502 CPU
2021-05-20 Refactored ADDR_VEC to ADDR_ALU so that it can support both zero page and interrupt/reset vectors
2021-05-22 Shorten dataBusMux to 2 bits because those are just the things that can be done in parallel with the ALU; widen aluResultStorage to 4 bits for some needed flexibility for zero page, indirect, indexin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
2021-05-24 Draft of relative branch instructions
2021-05-26 Add initial ALU tests for ALU_OP_COPY, ALU_OP_SBC, and ALU_OP_ADC; fix two's-complement behavior of SBC related to carry flag
2021-05-27 Tested working ADC in decimal mode, accurate to descriptions of the NMOS 6502
2021-05-27 Initial draft of Cpu6502 which encapsulates a Cpu6502MicrocodeRom and a Cpu65xxMicroArchitecture
2021-05-28 Add complete functional test against perfect6502 alone, based on https://github.com/amb5l/6502_65C02_functional_tests
2021-05-29 Fix a bunch of timing and edge bugs, implement new microcode for some new instructions to get us further along in the self test program
2021-05-29 Fix 'reserved' bit in P should always appear as '1'; fix PHP always sets B flag; fix PLA setting flags
2021-05-30 Implement a bunch of load and store opcodes for various addressing modes
2021-06-01 Implement INC/DEC opcodes
2021-06-01 Implement ADC and SBC in all addressing modes
2021-06-02 Implement undocumented NOP and JAM opcodes
2021-06-02 Implement and test undocumented instruction RLA in all of its addressing modes
2021-06-02 Implement and test undocumented instruction SAX in all of its addressing modes
2021-06-05 Implement and test undocumented instructions DCP, ISC, ANC, ALR, ARR, SBC, SBC_IMM_EB
2021-06-06 Implement and test undocumented instruction TAS
2021-06-09 Rough draft of VideoHorizontalStretch
2021-06-09 Fix math in blend() to allow it to use 100% of the left pixel's color
2021-06-10 Improve logic of upstreamResponseFifoReadEnable to look ahead to satisfying the next pixel, to achieve burst speeds of writing one downstream pixel per shader clock
2021-06-12 Fix cachedRowBIsOlder bug; VideoVerticalStretch now appears to be working
2021-06-13 Minimally tested and working VideoAggregateScaler with some unresolved issues still
2021-06-20 Implement arbitrary probability of downstream FIFO full to find bugs in FIFO handling in the video pipeline filters; fix design issue in VideoVerticalStretch where a pre-fetch of the pending downstre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
2021-08-29 Fix VideoHorizontalStretch logic for reading from pending downstream response fifo
2021-08-29 Minor cleanup after debugging VideoHorizontalStretch
2021-08-30 Reintroduce VideoPaddingFilter into VideoAggregateScaler, and fix a double-request bug that was hanging VideoHorizontalStretch and VideoPaddingFilter
2021-08-30 Fix typos
2021-09-04 Simplify padding pixel logic, reset screenRow and screenColumn as needed
2021-09-05 Add loading of glyph and screen RAM content from mem files to show defects better in TextOverlayGeneratorTests
2021-09-06 Add 8x14 font and use it in TextCharacterSet720p test
2021-09-13 Complete CP437 8x8 glyph set, and add TextOverlayGeneratorTests.TextCharacterSet240pNtsc
2021-09-14 Add TextOverlayGeneratorTests.AlphaBlendOverlays720p
2021-09-14 Initial commit of text-test SoC that just displays vertical lines on the screen for now
2021-09-14 Adjusted text overlay color alphas to be 0%, 50%, 75%, 100% based on appearance
2021-09-24 Added more PsramWishboneMasterTests and fixed NWAIT logic to indicate delayed ACK_I or ERR_I
2021-09-28 Redesign VideoGeneratorSource to support pipelined generator modules and respect responseFifoFull
2021-09-28 Remove misleading and ambiguous syncIsActiveLow signal
2021-09-30 Refactor VideoIntegerScale to use BlockRamDualPort for its two row caches
2021-09-30 Add BlockRamDualPort as a dependency for VideoVerticalStretch, VideoAggregateScaler, and VideoGeneratorPipeline
2021-10-01 Refactor VideoVerticalStretch to pipeline the downstream response stage and improve timing closure
2021-10-02 Improve timing closure for VideoHorizontalStretch by pipelining its blend calculation
2021-10-04 Add initial pipelined scanline functionality to VideoIntegerScale; some right edge glitching to work through still
2021-10-05 Improve timing closure of VideoVerticalStretch by adding an extra state with extra registers for calculated upstream rows
2021-10-06 Improve timing of VideoIntegerScale by adding a stage for upstream requests and by optimizing the stall condition for downstreamResponseFifoWriteEnable
2021-10-06 Improve timing of VideoHorizontalStretch by adding a downstream response stage to pre-calculate the left and right pixel columns and coefficients
2021-10-08 Refactor SyncFifo and AsyncFifo to use BlockRamDualPort so that synthesis tools can infer block RAMs and potentially save on other FPGA resources
2021-10-08 Improve timing of VideoIntegerScale by staging pendingUpstreamRequestFifoReadData and pendingDownstreamResponseFifoReadData
2021-10-08 Improve timing of VideoIntegerScale by staging downstreamCacheRowIsCacheA/B flags
2021-10-08 Improve timing of VideoPaddingFilter by implementing a downstream response pipeline
2021-10-08 Improve timing of VideoHorizontalStretch by adding a pipeline stage to sum the color weights
2021-10-09 Fix downstream request bug in VideoHorizontalStretch
2021-10-10 Introduce CRC checks of output framebuffer for certain tests, to better detect when a bug screws up the output image
2021-10-11 Comment out trace in TextOverlayGeneratorTests
2021-10-12 Improve timing of VideoVerticalStretch, VideoHorizontalStretch, VideoPaddingFilter
2021-10-13 Add probability of empty to BmpPipelineSource
2021-10-13 Added ColorPattern720pUpscaleScanlines and commented-out ColorPattern720pBinning
2021-12-29 Add features to DualPortBlockRam; update verilator, gtest, cmake, etc.
    DualPortBlockRam was refactored somewhat to include more features, like resettable data outputs and byte-wide write enable. This required an update to Verilator, which required an update to MSYS2, wh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

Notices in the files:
pcb/rise/reclone-rise.brd:
©2017 reclonelabs.com
Rev. A (CC BY 4.0)
parts and their libraries:
SparkFun-Passives: Licensing: Creative Commons ShareAlike 4.0 International - https://creativecommons.org/licenses/by-sa/4.0
